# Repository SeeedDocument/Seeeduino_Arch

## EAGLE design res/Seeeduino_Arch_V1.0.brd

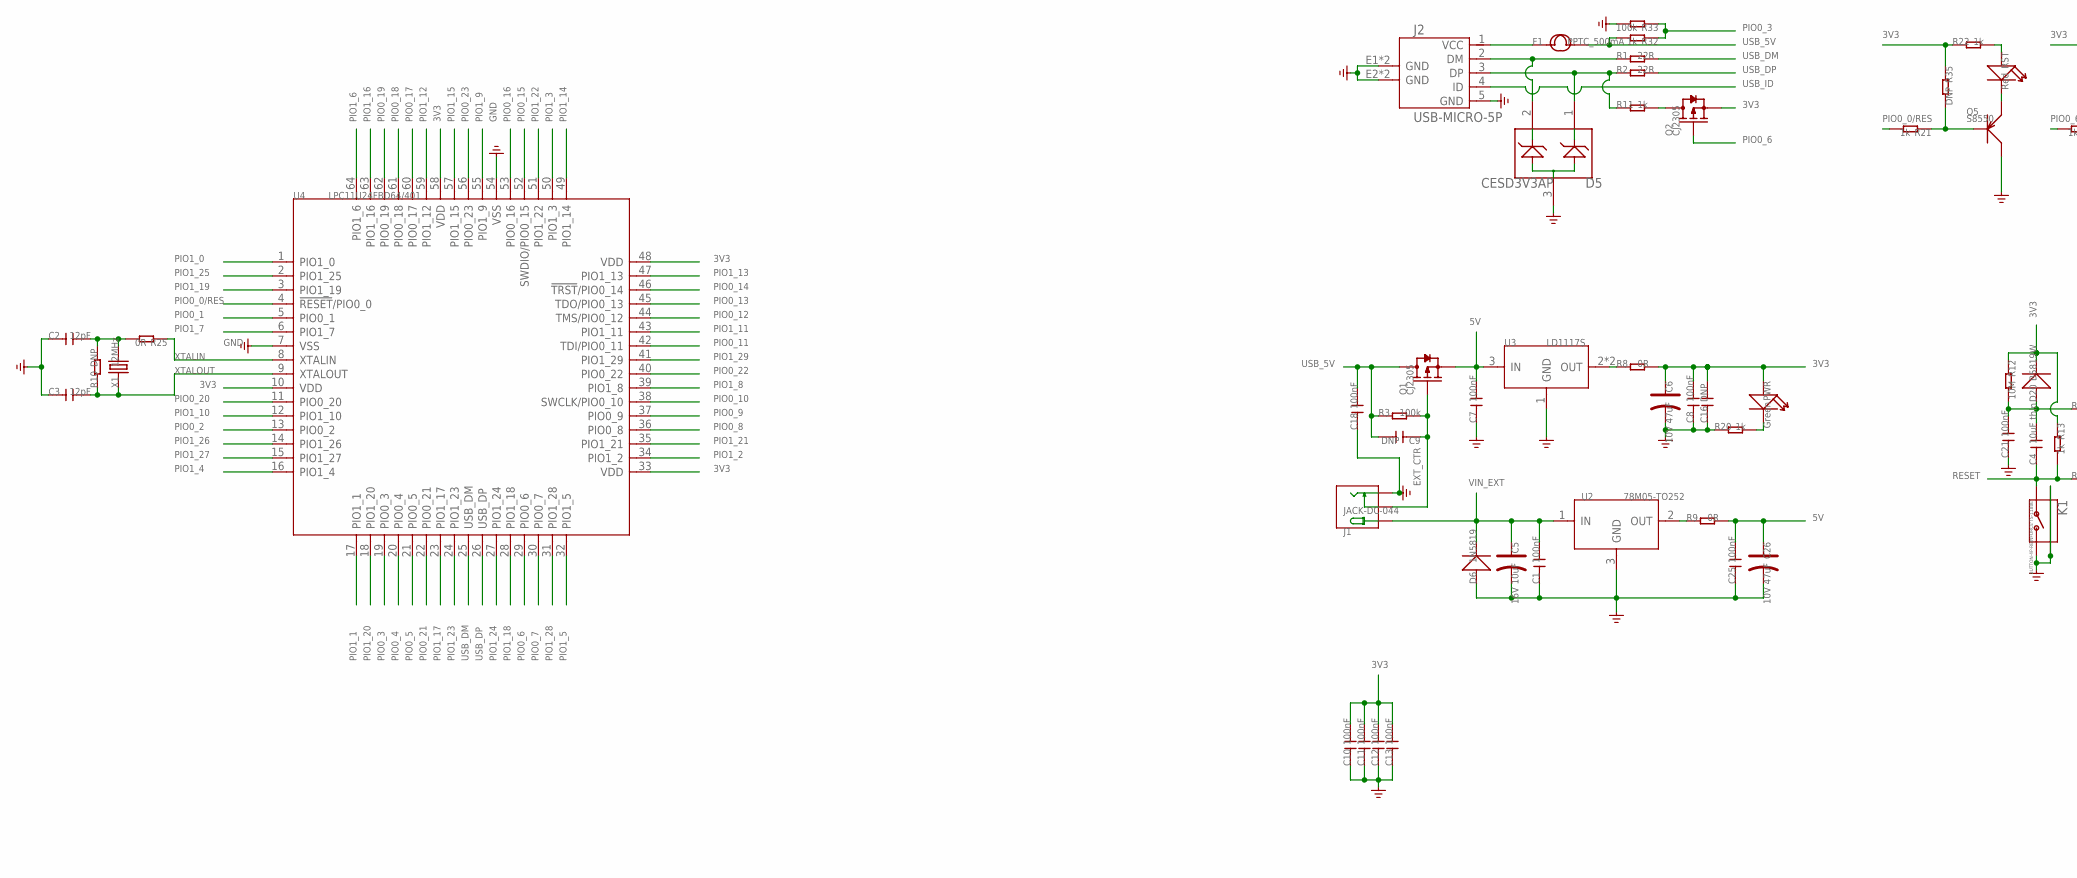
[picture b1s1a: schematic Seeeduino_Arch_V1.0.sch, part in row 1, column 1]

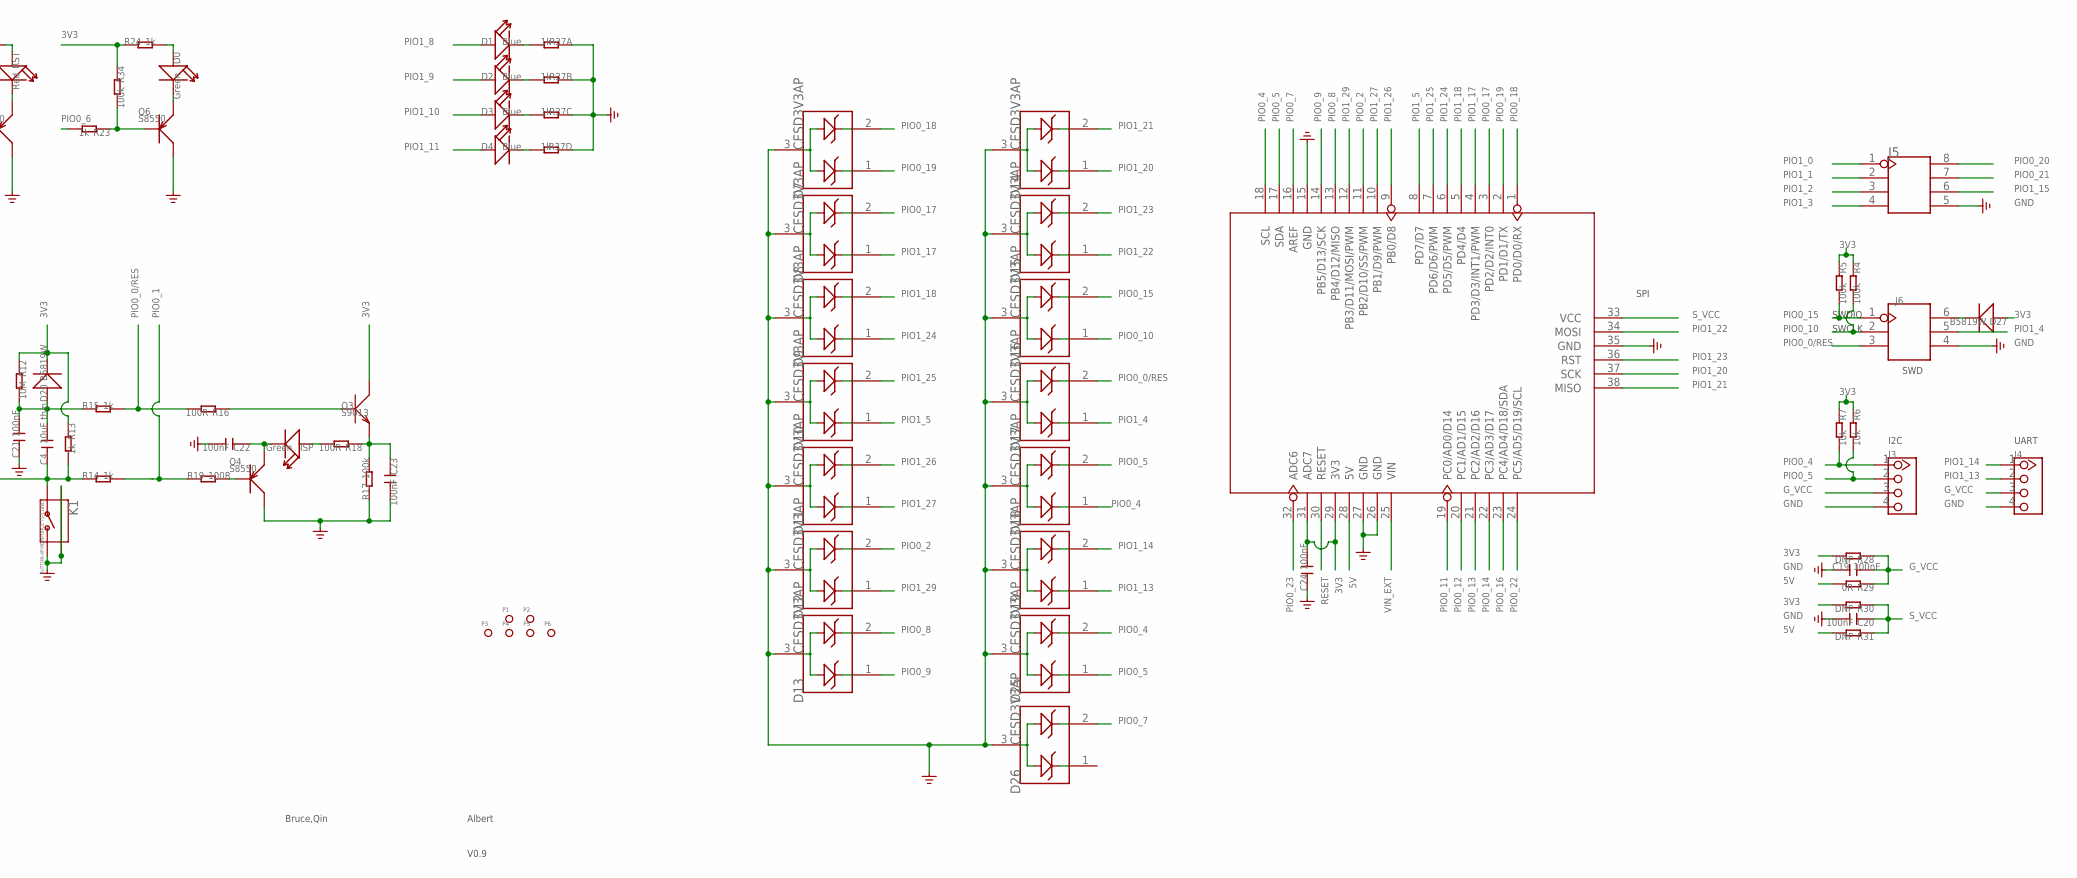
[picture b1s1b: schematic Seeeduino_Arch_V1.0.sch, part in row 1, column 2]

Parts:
C1, C7, C8, C10, C11, C12, C13, C18, C19, C20, C21, C22, C23, C24, C25: 100nF; C0603
C2, C3: 12pF; C0603
C4: 10uF thin; C0805
C5: 16V 10uF; AVX-B
C6, C26: 10V 47uF; AVX-B
C9, C16: DNP; C0603
D0: Green; LED-0603
D1, D2, D3, D4: Blue; LED-0603
D5, D7, D8, D9, D10, D11, D12, D13, D14, D15, D16, D17, D18, D19, D25, D26: CESD3V3AP; SOT23
D6: 1N5819; SMA
D20, D27: B5819W; SOD123
F1: PPTC_500mA; F1206
ISP: Green; LED-0603
J1: JACK-DC-044; DC-044
J2: USB-MICRO-5P; MICRO-USB-5P
J3, J4: TWIG-4P-2.0-2.0; 4P-2.0
J5: HEADER-2X4P-2.54; 2X4P-2.54
J6: HEADER-2X3P-2.54; 2X3P-2.54
K1: BUTTON-4P-REINFORCE'TS-1188E'; 4P-SMD-7X3.5X3.5H
P1, P2, P3, P4, P5, P6: PAD-MARK; ROUND-MARK-1.0
PWR: Green; LED-0603
Q1, Q2: CJ2305; SOT23
Q3: S9013; SOT23
Q4, Q5, Q6: S8550; SOT23
R1, R2: 22R; R0603
R3, R4, R5, R17, R33, R34: 100k; R0603
R6, R7: 10k; R0603
R8, R9, R25, R29: 0R; R0603
R10, R28, R30, R31, R35: DNP; R0603
R11, R13, R14, R15, R20, R21, R22, R23, R24, R32: 1k; R0603
R12: 10M; R0603
R16, R18, R19: 100R; R0603
R37: 1k; 1206-8-3.3X2.4
RST: Red; LED-0603
U1: ARDUINO-38P
U2: 78M05-TO252; TO252
U3: LD1117S; SOT-223
U4: LPC11U24FBD64/401; LQFP64
X1: 12MHz; 2P-SMD-5X3.2

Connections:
3V3: C6.+, C8.2, C10.2, C11.2, C12.2, C13.2, C16.2, C24.2, D20.-, D27.+, PWR.+, Q2.2 (S), Q3.3 (C), R4.1, R5.1, R6.1, R7.1, R8.2, R12.1, R13.1, R22.1, R24.1, R28.2, R30.2, R34.1, R35.1, U1.29 (3V3), U1.31 (ADC7), U4.10 (VDD), U4.33 (VDD), U4.48 (VDD), U4.58 (VDD)
5V: C7.2, C25.2, C26.+, Q1.2 (S), R9.2, R29.2, R31.2, U1.28 (5V), U3.3 (IN)
EXT_CTR: C9.1, J1.CDN, Q1.1 (G), R3.2
GND: C1.1, C2.1, C3.1, C5.-, C6.-, C7.1, C8.1, C10.1, C11.1, C12.1, C13.1, C16.1, C18.1, C19.1, C20.2, C21.1, C22.2, C23.2, C24.1, C25.1, C26.-, D5.3, D6.2 (+), D7.3, D8.3, D9.3, D10.3, D11.3, D12.3, D13.3, D14.3, D15.3, D16.3, D17.3, D18.3, D19.3, D25.3, D26.3, J1.-, J2.5 (GND), J2.E1 (GND), J2.E2 (GND), J2.P1 (GND), J2.P2 (GND), J3.4, J4.4, J5.5, J6.4, K1.2, K1.S1, K1.S2, Q4.3 (C), Q5.3 (C), Q6.3 (C), R17.1, R20.1, R33.2, R37.1, R37.2 (1), R37.3 (1), R37.4 (1), U1.15 (GND), U1.26 (GND), U1.27 (GND), U1.35 (GND), U2.3 (GND), U3.1 (GND), U4.7 (VSS), U4.54 (VSS)
G_VCC: C19.2, J3.3, J4.3, R28.1, R29.1
unnamed: D27.-, J6.6
unnamed: D4.-, R37.5 (2)
unnamed: Q2.3 (D), R11.2
unnamed: Q3.1 (B), R16.1
unnamed: C23.1, Q3.2 (E), R17.2, R18.1
unnamed: C4.2, C21.2, D20.+, R12.2, R15.1
unnamed: PWR.-, R20.2
unnamed: Q5.1 (B), R21.1, R35.2
unnamed: ISP.+, R18.2
unnamed: C22.1, ISP.-, Q4.2 (E)
unnamed: Q4.1 (B), R19.2
unnamed: Q5.2 (E), RST.-
unnamed: R22.2, RST.+
unnamed: Q6.1 (B), R23.1, R34.2
unnamed: D0.-, Q6.2 (E)
unnamed: D3.-, R37.6 (2)
unnamed: D0.+, R24.2
unnamed: D2.-, R37.7 (2)
unnamed: C2.2, R10.2, R25.2, X1.2
unnamed: D1.-, R37.8 (2)
unnamed: R8.1, U3.2 (OUT), U3.TER (OUT)
unnamed: D5.2, J2.2 (DM), R1.1
unnamed: D5.1, J2.3 (DP), R2.1, R11.1
unnamed: F1.1, J2.1 (VCC)
unnamed: R9.1, U2.2 (OUT)
PIO0_0/RES: D17.2, J6.3, R15.2, R16.2, R21.2, U4.4 (!RESET!/PIO0_0)
PIO0_1: R14.2, R19.1, U4.5 (PIO0_1)
PIO0_2: D12.2, U1.11 (PB2/D10/SS/PWM), U4.13 (PIO0_2)
PIO0_3: R32.1, R33.1, U4.19 (PIO0_3)
PIO0_4: D18.1, D25.2, J3.1, R7.2, U1.18 (SCL), U4.20 (PIO0_4)
PIO0_5: D18.2, D25.1, J3.2, R6.2, U1.17 (SDA), U4.21 (PIO0_5)
PIO0_6: Q2.1 (G), R23.2, U4.29 (PIO0_6)
PIO0_7: D26.2, U1.16 (AREF), U4.30 (PIO0_7)
PIO0_8: D13.2, U1.13 (PB4/D12/MISO), U4.36 (PIO0_8)
PIO0_9: D13.1, U1.14 (PB5/D13/SCK), U4.37 (PIO0_9)
PIO0_10: D16.1, J6.2, R4.2, U4.38 (SWCLK/PIO0_10)
PIO0_11: U1.19 (PC0/AD0/D14), U4.42 (TDI/PIO0_11)
PIO0_12: U1.20 (PC1/AD1/D15), U4.44 (TMS/PIO0_12)
PIO0_13: U1.21 (PC2/AD2/D16), U4.45 (TDO/PIO0_13)
PIO0_14: U1.22 (PC3/AD3/D17), U4.46 (!TRST!/PIO0_14)
PIO0_15: D16.2, J6.1, R5.2, U4.52 (SWDIO/PIO0_15)
PIO0_16: U1.23 (PC4/AD4/D18/SDA), U4.53 (PIO0_16)
PIO0_17: D8.2, U1.3 (PD2/D2/INT0), U4.60 (PIO0_17)
PIO0_18: D7.2, U1.1 (PD0/D0/RX), U4.61 (PIO0_18)
PIO0_19: D7.1, U1.2 (PD1/D1/TX), U4.62 (PIO0_19)
PIO0_20: J5.8, U4.11 (PIO0_20)
PIO0_21: J5.7, U4.22 (PIO0_21)
PIO0_22: U1.24 (PC5/AD5/D19/SCL), U4.40 (PIO0_22)
PIO0_23: U1.32 (ADC6), U4.56 (PIO0_23)
PIO1_0: J5.1, U4.1 (PIO1_0)
PIO1_1: J5.2, U4.17 (PIO1_1)
PIO1_2: J5.3, U4.34 (PIO1_2)
PIO1_3: J5.4, U4.50 (PIO1_3)
PIO1_4: D17.1, J6.5, U4.16 (PIO1_4)
PIO1_5: D10.1, U1.8 (PD7/D7), U4.32 (PIO1_5)
PIO1_6: U4.64 (PIO1_6)
PIO1_7: U4.6 (PIO1_7)
PIO1_8: D1.+, U4.39 (PIO1_8)
PIO1_9: D2.+, U4.55 (PIO1_9)
PIO1_10: D3.+, U4.12 (PIO1_10)
PIO1_11: D4.+, U4.43 (PIO1_11)
PIO1_12: U4.59 (PIO1_12)
PIO1_13: D19.1, J4.2, U4.47 (PIO1_13)
PIO1_14: D19.2, J4.1, U4.49 (PIO1_14)
PIO1_15: J5.6, U4.57 (PIO1_15)
PIO1_16: U4.63 (PIO1_16)
PIO1_17: D8.1, U1.4 (PD3/D3/INT1/PWM), U4.23 (PIO1_17)
PIO1_18: D9.2, U1.5 (PD4/D4), U4.28 (PIO1_18)
PIO1_19: U4.3 (PIO1_19)
PIO1_20: D14.1, U1.37 (SCK), U4.18 (PIO1_20)
PIO1_21: D14.2, U1.38 (MISO), U4.35 (PIO1_21)
PIO1_22: D15.1, U1.34 (MOSI), U4.51 (PIO1_22)
PIO1_23: D15.2, U1.36 (RST), U4.24 (PIO1_23)
PIO1_24: D9.1, U1.6 (PD5/D5/PWM), U4.27 (PIO1_24)
PIO1_25: D10.2, U1.7 (PD6/D6/PWM), U4.2 (PIO1_25)
PIO1_26: D11.2, U1.9 (PB0/D8), U4.14 (PIO1_26)
PIO1_27: D11.1, U1.10 (PB1/D9/PWM), U4.15 (PIO1_27)
PIO1_28: U4.31 (PIO1_28)
PIO1_29: D12.1, U1.12 (PB3/D11/MOSI/PWM), U4.41 (PIO1_29)
RESET: C4.1, K1.1, R13.2, R14.1, U1.30 (RESET)
S_VCC: C20.1, R30.1, R31.1, U1.33 (VCC)
USB_5V: C9.2, C18.2, F1.2, Q1.3 (D), R3.1, R32.2
USB_DM: R1.2, U4.25 (USB_DM)
USB_DP: R2.2, U4.26 (USB_DP)
USB_ID: J2.4 (ID)
VIN_EXT: C1.2, C5.+, D6.1 (-), J1.+, U1.25 (VIN), U2.1 (IN)
XTALIN: R25.1, U4.8 (XTALIN)
XTALOUT: C3.2, R10.1, U4.9 (XTALOUT), X1.1

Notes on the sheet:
Bruce,Qin
Albert
V0.9
I2C
UART
SWD
SPI
SWDIO
SWCLK

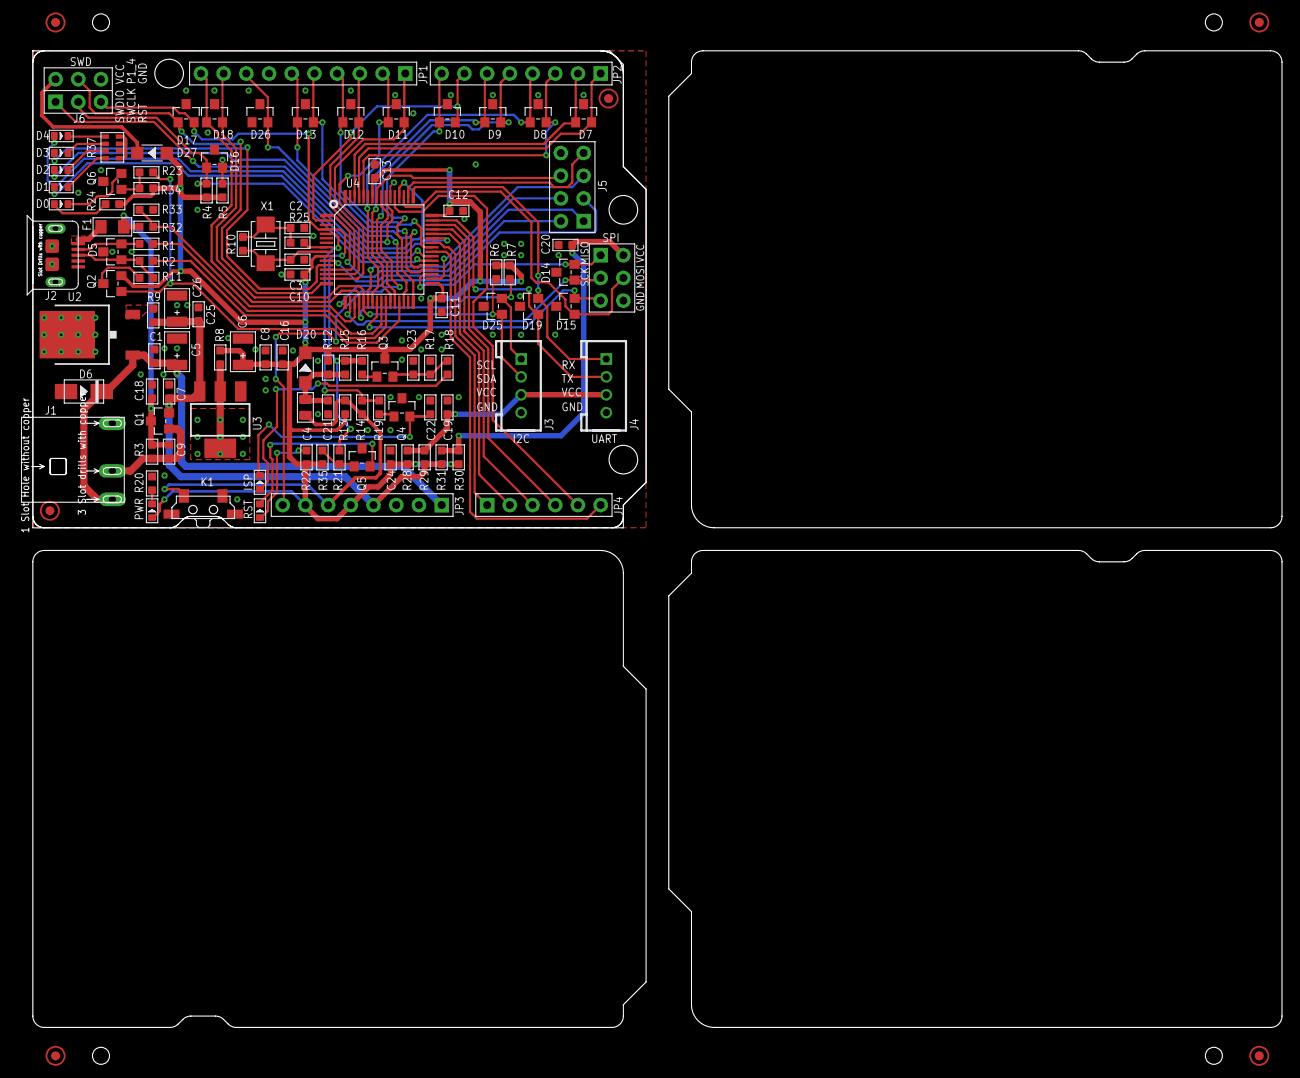
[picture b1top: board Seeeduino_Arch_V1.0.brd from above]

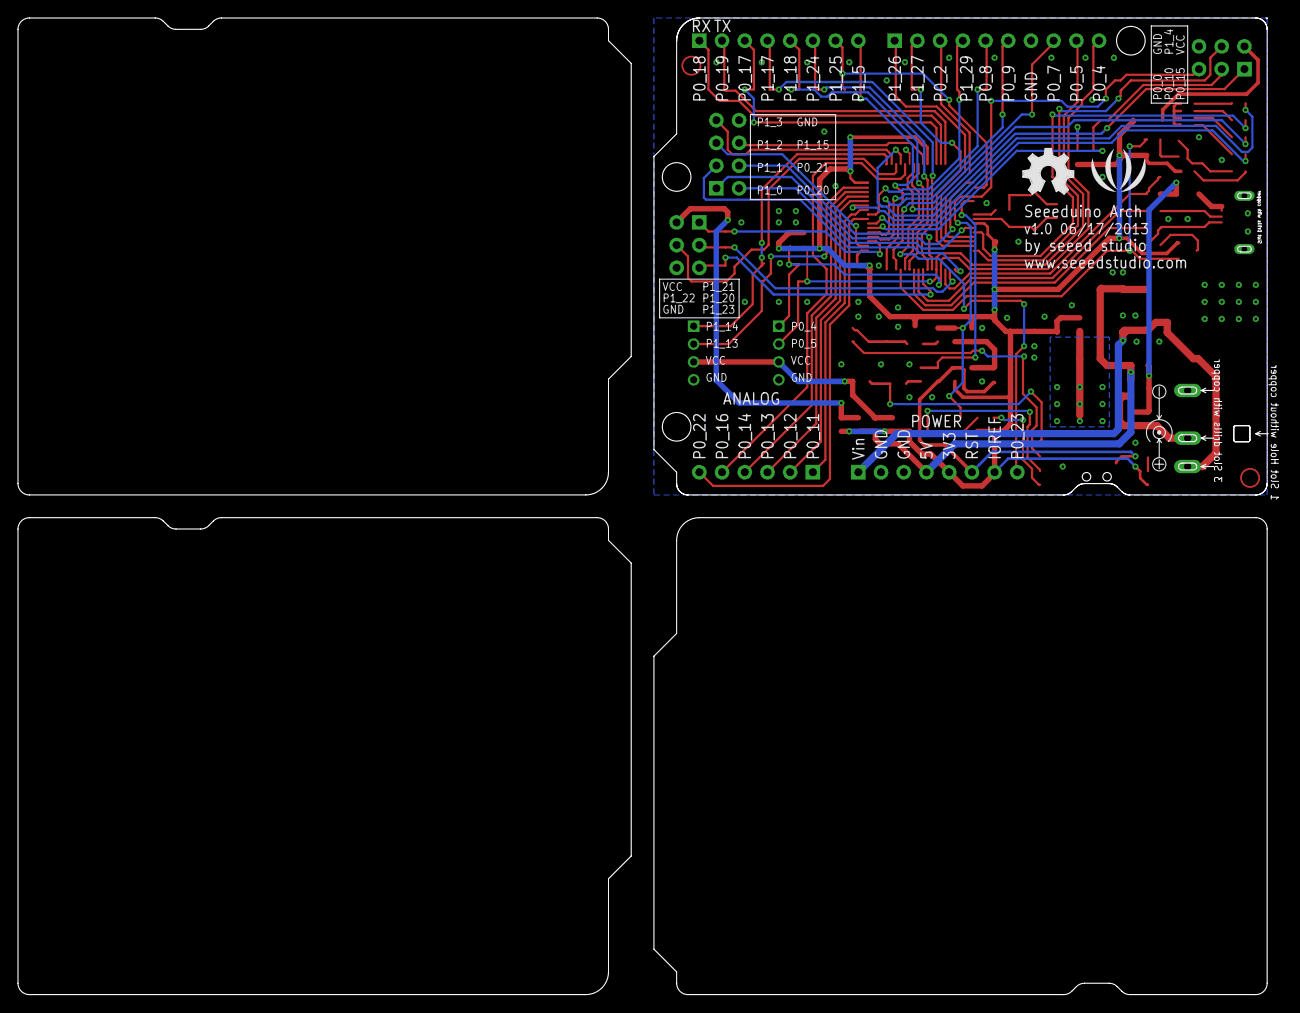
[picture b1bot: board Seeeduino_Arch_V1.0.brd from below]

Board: 2 copper layers, 141.3 x 109.1 mm, 111 parts (2 on the bottom side), 86 nets.

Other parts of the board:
U$33: OSHW_FILLX200_NOTEXT
U$34: LOGO_SILK

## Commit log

2017-06-13 upgrade
